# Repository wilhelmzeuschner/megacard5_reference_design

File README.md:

# Reference Design for MegaCard 5 Carrier Board
**Further documentation avaiable at: www.wizeus.de/megacard5-docs**
Reference design for the MegaCard 5 100 Mbit/s Ethernet Switch Carrier Board.

The design is done in KiCad. All KiCad files are included in this repo.

## PDF Schematic
The pdf schematic is available here: https://github.com/wilhelmzeuschner/megacard5_reference_design/blob/main/doc/megacard5_reference_design.pdf

## PCB images

Please note that the picture shows Rev. 1.0 of the PCB. The render shows Rev. 1.1.

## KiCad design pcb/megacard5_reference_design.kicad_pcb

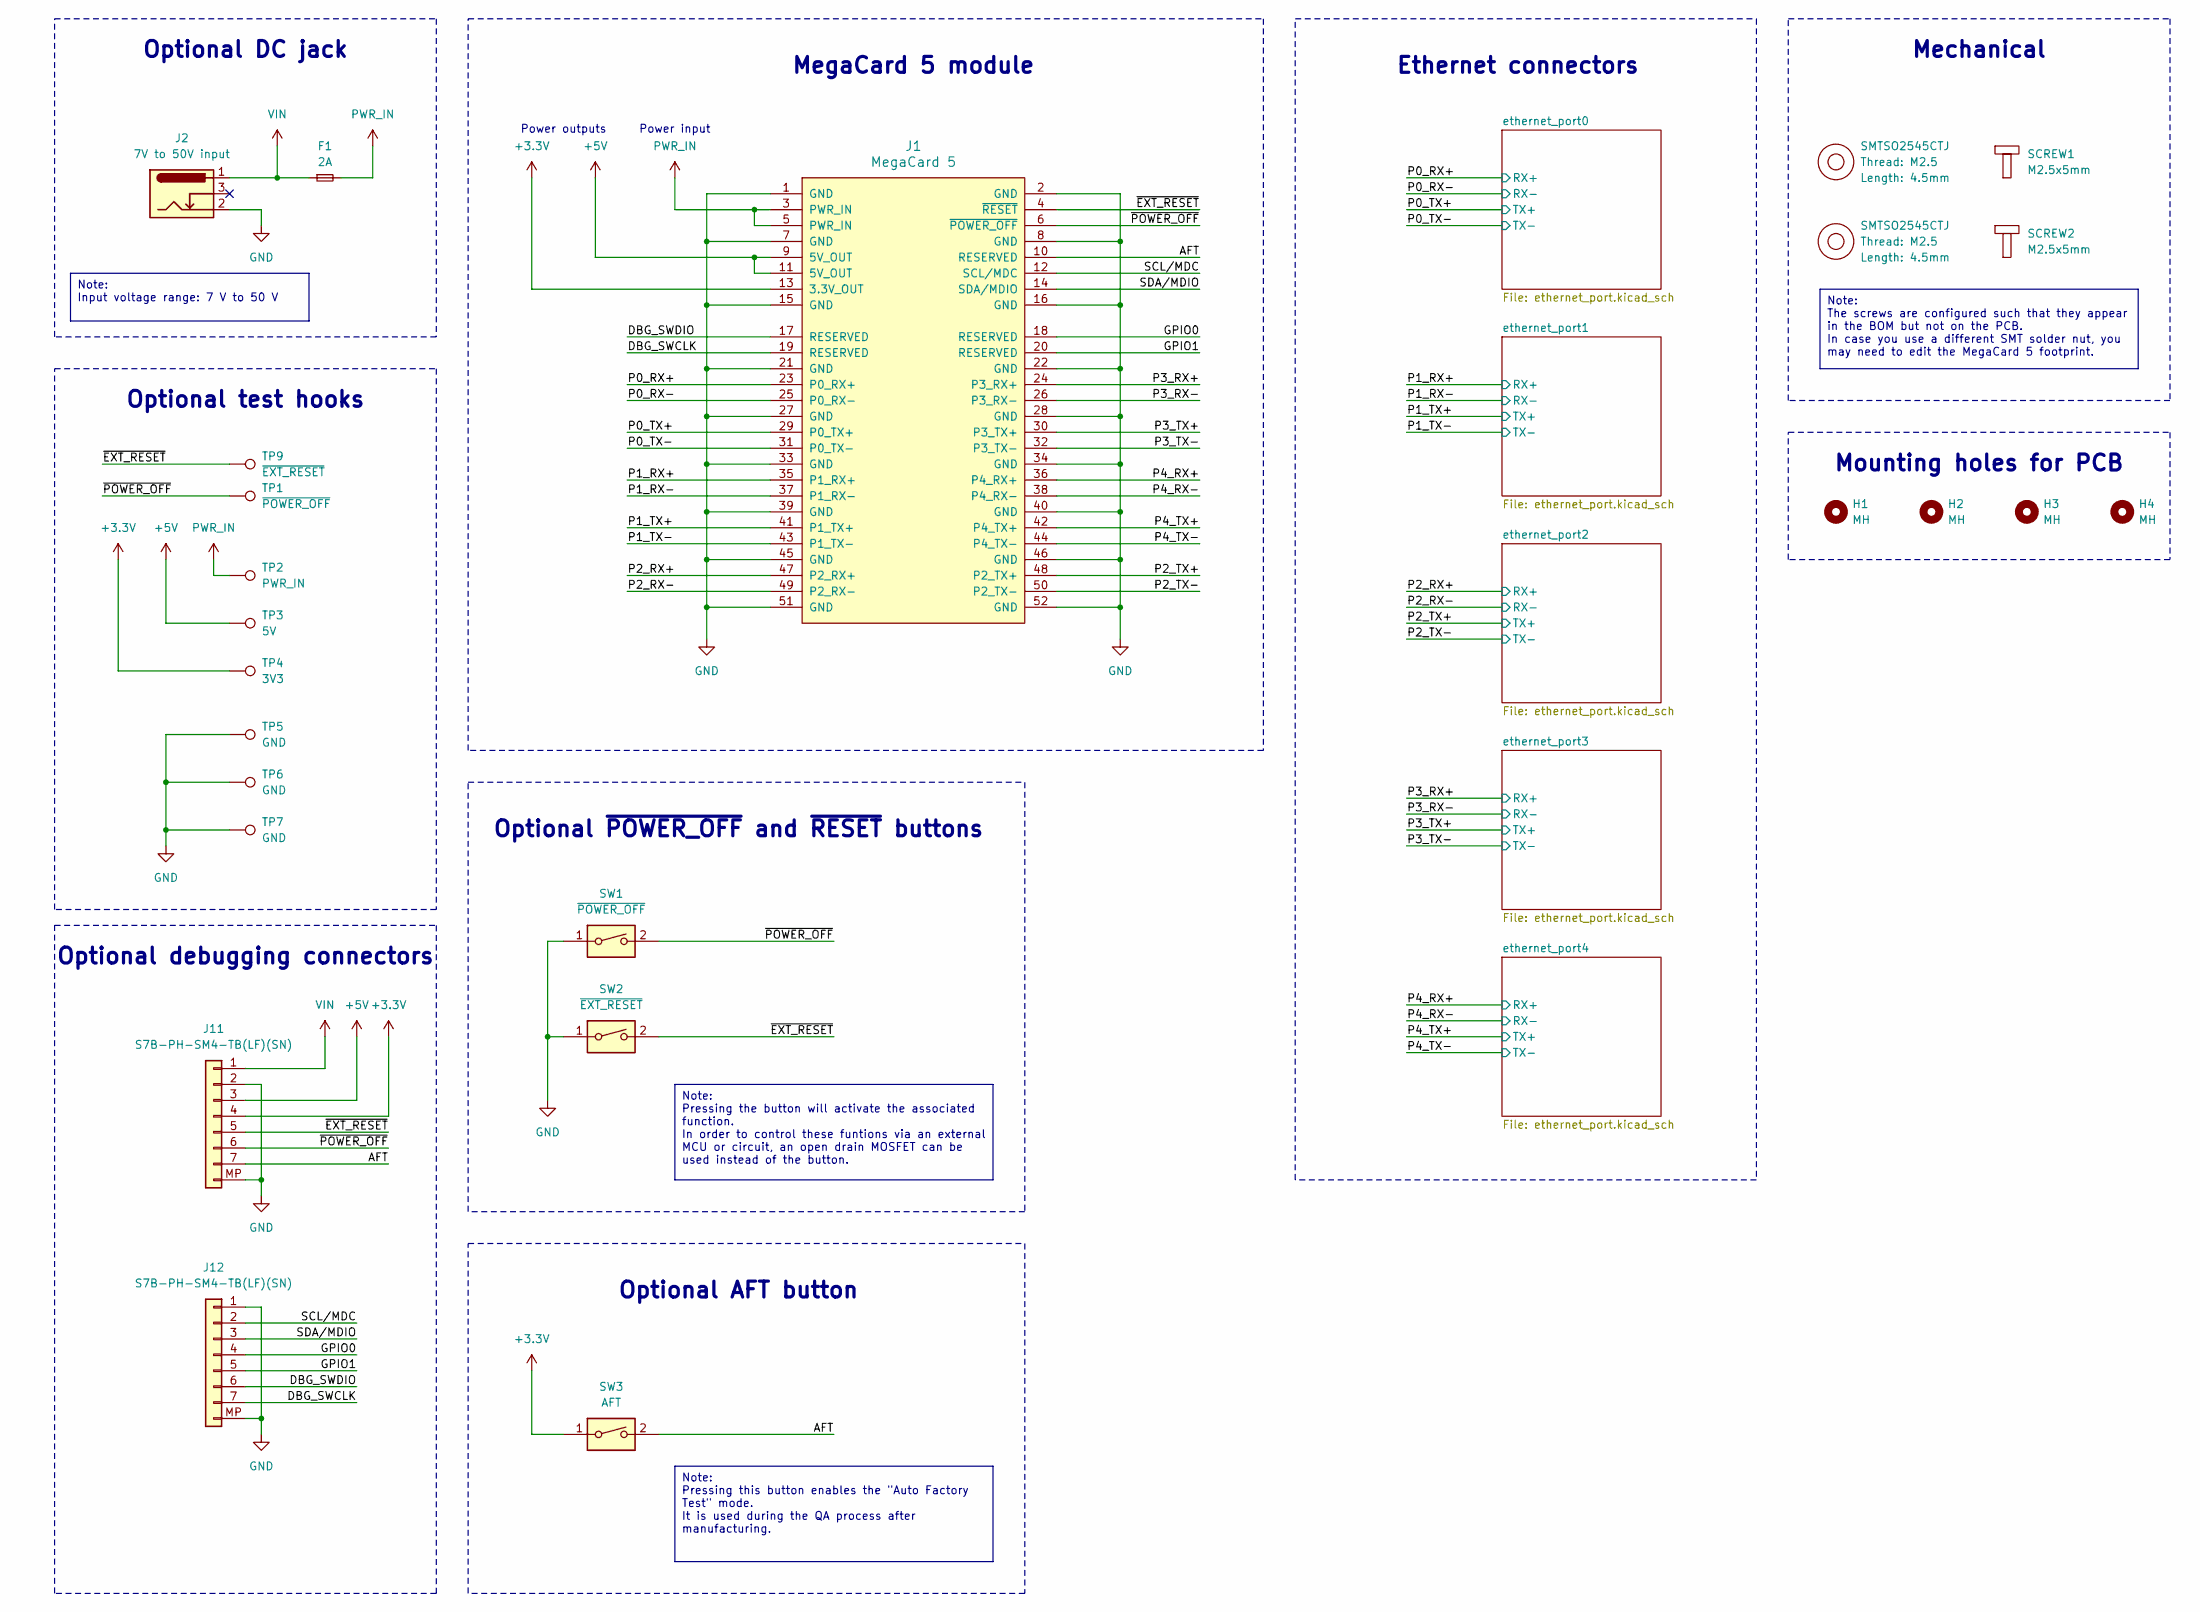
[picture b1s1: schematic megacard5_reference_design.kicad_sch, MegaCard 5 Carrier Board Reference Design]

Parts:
F1: 2A; Fuse_1206_3216Metric; LCSC PN C3105
H1, H2, H3, H4: MH; MountingHole_3.2mm_M3_DIN965
J1: MegaCard 5; MegaCard_5; LCSC PN C428485
J2: 7V to 50V input; DC-005-5A-2.0-SMT; LCSC PN C319134
J10, J13: SMTSO2545CTJ; LCSC PN C2916325
J11, J12: S7B-PH-SM4-TB(LF)(SN); JST_PH_S7B-PH-SM4-TB_1x07-1MP_P2.00mm_Horizontal; LCSC PN C265453
SCREW1, SCREW2: M2.5x5mm; LCSC PN C5183547
SW1: ~{POWER_OFF}; SKRPACE010; LCSC PN C139797
SW2: ~{EXT_RESET}; SKRPACE010; LCSC PN C139797
SW3: AFT; SKRPACE010; LCSC PN C139797
TP1: ~{POWER_OFF}; 5019; LCSC PN C5199800
TP2: PWR_IN; 5019; LCSC PN C5199800
TP3: 5V; 5019; LCSC PN C5199800
TP4: 3V3; 5019; LCSC PN C5199800
TP5, TP6, TP7: GND; 5019; LCSC PN C5199800
TP9: ~{EXT_RESET}; 5019; LCSC PN C5199800

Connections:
+3.3V: J1.13 (3.3V_OUT), J11.4, SW3.1, TP4.1
+5V: J1.9 (5V_OUT), J1.11 (5V_OUT), J11.3, TP3.1
/AFT: J1.10 (RESERVED), J11.7, SW3.2
/DBG_SWCLK: J1.19 (RESERVED), J12.7
/DBG_SWDIO: J1.17 (RESERVED), J12.6
/GPIO0: J1.18 (RESERVED), J12.4
/GPIO1: J1.20 (RESERVED), J12.5
/P0_RX+: J1.23 (P0_RX+); also elsewhere on the board
/P0_RX-: J1.25 (P0_RX-); also elsewhere on the board
/P0_TX+: J1.29 (P0_TX+); also elsewhere on the board
/P0_TX-: J1.31 (P0_TX-); also elsewhere on the board
/P1_RX+: J1.35 (P1_RX+); also elsewhere on the board
/P1_RX-: J1.37 (P1_RX-); also elsewhere on the board
/P1_TX+: J1.41 (P1_TX+); also elsewhere on the board
/P1_TX-: J1.43 (P1_TX-); also elsewhere on the board
/P2_RX+: J1.47 (P2_RX+); also elsewhere on the board
/P2_RX-: J1.49 (P2_RX-); also elsewhere on the board
/P2_TX+: J1.48 (P2_TX+); also elsewhere on the board
/P2_TX-: J1.50 (P2_TX-); also elsewhere on the board
/P3_RX+: J1.24 (P3_RX+); also elsewhere on the board
/P3_RX-: J1.26 (P3_RX-); also elsewhere on the board
/P3_TX+: J1.30 (P3_TX+); also elsewhere on the board
/P3_TX-: J1.32 (P3_TX-); also elsewhere on the board
/P4_RX+: J1.36 (P4_RX+); also elsewhere on the board
/P4_RX-: J1.38 (P4_RX-); also elsewhere on the board
/P4_TX+: J1.42 (P4_TX+); also elsewhere on the board
/P4_TX-: J1.44 (P4_TX-); also elsewhere on the board
/SCL/MDC: J1.12 (SCL/MDC), J12.2
/SDA/MDIO: J1.14 (SDA/MDIO), J12.3
/~EXT_RESET: J1.4 (~RESET), J11.5, SW2.2, TP9.1
/~POWER_OFF: J1.6 (~POWER_OFF), J11.6, SW1.2, TP1.1
GND: J1.1 (GND), J1.2 (GND), J1.7 (GND), J1.8 (GND), J1.15 (GND), J1.16 (GND), J1.21 (GND), J1.22 (GND), J1.27 (GND), J1.28 (GND), J1.33 (GND), J1.34 (GND), J1.39 (GND), J1.40 (GND), J1.45 (GND), J1.46 (GND), J1.51 (GND), J1.52 (GND), J2.2, J11.2, J11.MP, J12.1, J12.MP, SW1.1, SW2.1, TP5.1, TP6.1, TP7.1; also elsewhere on the board
PWR_IN: F1.2, J1.3 (PWR_IN), J1.5 (PWR_IN), TP2.1
VIN: F1.1, J2.1, J11.1

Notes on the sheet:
Note: Pressing the button will activate the associated function. In order to control these funtions via an external MCU or circuit, an open drain MOSFET can be used instead of the button.
Note: The screws are configured such that they appear in the BOM but not on the PCB. In case you use a different SMT solder nut, you may need to edit the MegaCard 5 footprint.
Note: Input voltage range: 7 V to 50 V
Note: Pressing this button enables the "Auto Factory Test" mode. It is used during the QA process after manufacturing.
Optional debugging connectors
Optional ~{POWER_OFF} and ~{RESET} buttons
Power input
Optional DC jack
Ethernet connectors
Mechanical
Mounting holes for PCB
MegaCard 5 module
Optional AFT button
Power outputs
Optional test hooks

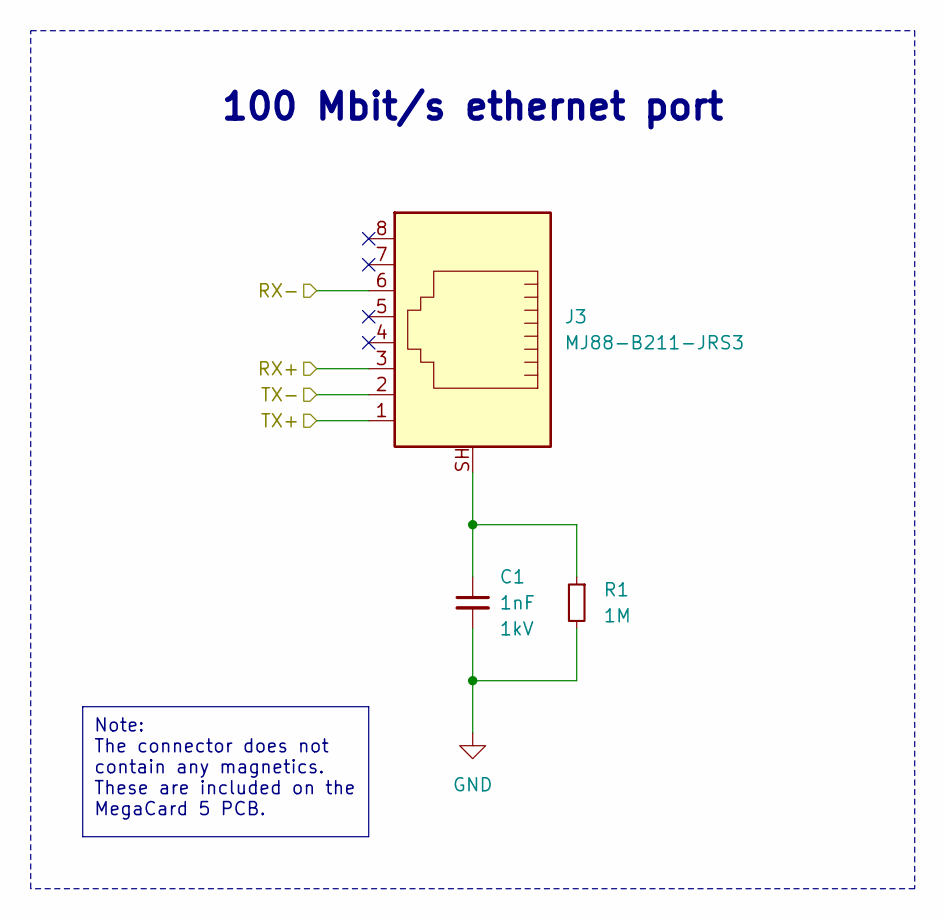
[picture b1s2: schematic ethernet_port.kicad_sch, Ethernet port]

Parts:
C1: 1nF; C_1206_3216Metric; Voltage 1kV; LCSC PN C23631
J3: MJ88-B211-JRS3; LCSC PN C2895614
R1: 1M; R_1206_3216Metric; LCSC PN C148194

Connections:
/P0_RX+: J3.3; also elsewhere on the board
/P0_RX-: J3.6; also elsewhere on the board
/P0_TX+: J3.1; also elsewhere on the board
/P0_TX-: J3.2; also elsewhere on the board
GND: C1.2, R1.2; also elsewhere on the board
unnamed: C1.1, J3.SH, R1.1

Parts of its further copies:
C2, C3, C4, C5: 1nF; C_1206_3216Metric; Voltage 1kV; LCSC PN C23631
J4, J5, J6, J7: MJ88-B211-JRS3; LCSC PN C2895614
R2, R3, R4, R5: 1M; R_1206_3216Metric; LCSC PN C148194

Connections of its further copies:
/P1_RX+: J4.3; also elsewhere on the board
/P1_RX-: J4.6; also elsewhere on the board
/P1_TX+: J4.1; also elsewhere on the board
/P1_TX-: J4.2; also elsewhere on the board
/P2_RX+: J5.3; also elsewhere on the board
/P2_RX-: J5.6; also elsewhere on the board
/P2_TX+: J5.1; also elsewhere on the board
/P2_TX-: J5.2; also elsewhere on the board
/P3_RX+: J6.3; also elsewhere on the board
/P3_RX-: J6.6; also elsewhere on the board
/P3_TX+: J6.1; also elsewhere on the board
/P3_TX-: J6.2; also elsewhere on the board
/P4_RX+: J7.3; also elsewhere on the board
/P4_RX-: J7.6; also elsewhere on the board
/P4_TX+: J7.1; also elsewhere on the board
/P4_TX-: J7.2; also elsewhere on the board
GND: C2.2, C3.2, C4.2, C5.2, R2.2, R3.2, R4.2, R5.2; also elsewhere on the board
unnamed: C2.1, J4.SH, R2.1
unnamed: C3.1, J5.SH, R3.1
unnamed: C4.1, J6.SH, R4.1
unnamed: C5.1, J7.SH, R5.1

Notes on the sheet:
Note: The connector does not contain any magnetics. These are included on the MegaCard 5 PCB.
100 Mbit/s ethernet port

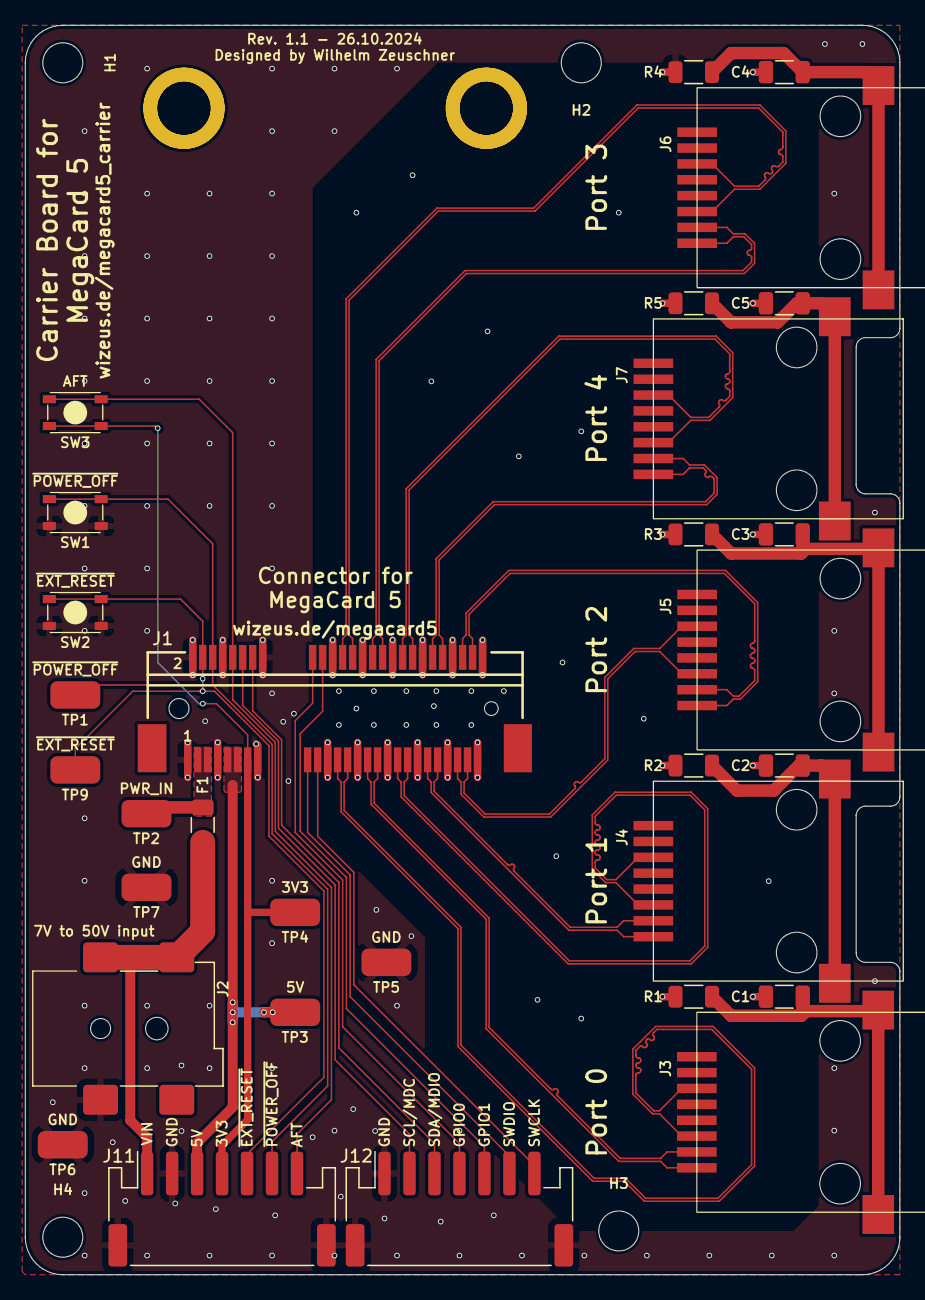
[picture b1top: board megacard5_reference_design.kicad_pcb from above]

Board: 4 copper layers, 70.0 x 100.0 mm, 37 parts (0 on the bottom side), 39 nets.

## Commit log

2024-09-14 Update LICENSE
2024-09-14 added project structure
2024-09-15 PCBs ordered v1.0
2024-10-26 added doc link
2024-10-26 image
2024-10-26 updated PCB to Rev 1.1
2024-10-26 added pdf schematic
2024-10-26 renamed VCC to PWR_IN
2024-10-27 update drawing
2024-10-27 add 3D models
2024-10-27 added pinouts
2024-10-27 added technical drawings
